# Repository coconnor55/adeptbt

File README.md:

# AdeptBT

Credit-card sized nRF52840 control board (Raytac MDBT50Q-1MV2).

## Features

- Dual TMC2209 stepper drivers
- Two 2N2222 low-side outputs with jumperable V+ (3.3 V / VIN)
- USB-C programming; LiPo (JST) with ~400–500 mA charge; VIN 5–18 V (P-FET + TVS + PPTC)
- Analog header (4× AIN at 3.3 V; external divider if needed) and digital GPIO header
- 6-pin screw terminals: steppers (`A1 A2 B1 B2 VM GND`) and power/outs (`VIN GND V+ OUT1 V+ OUT2`)

## Hardware

KiCad project: [`hardware/`](hardware/) — schematic, PCB placement, silkscreen (rev 2.0).

See [`docs/DESIGN.md`](docs/DESIGN.md), [`docs/STACKUP.md`](docs/STACKUP.md), [`docs/DECOUPLING.md`](docs/DECOUPLING.md), [`docs/JLCPCB_BOM.md`](docs/JLCPCB_BOM.md), [`hardware/README.md`](hardware/README.md). Repo decisions and open work: [`memory/`](memory/).

Open `hardware/adeptbt.kicad_pro` in KiCad 10 to finish power discretes, routing, and Gerbers.

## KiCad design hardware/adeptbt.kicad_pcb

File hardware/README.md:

# AdeptBT hardware (rev 2.0)

KiCad 10 project — JLCPCB-first. Schematic: `tools/gen_adeptbt_sch.py` if needed. **PCB placement is owned by pcbnew** (`adeptbt.kicad_pcb`). Do not run `tools/gen_adeptbt_pcb.py` — it refuses to write.

| File | Purpose |
|------|---------|
| `adeptbt.kicad_pro` | Project |
| `adeptbt.kicad_sch` | Wired schematic (global labels + GPIO lock) |
| `adeptbt.kicad_pcb` | Board (edit in KiCad; source of truth for placement) |
| `fp-lib-table` / `sym-lib-table` | AdeptBT + jlc libraries |
| `libs/AdeptBT.pretty/` | TE 3.81 mm screw, barrel 5.5×2.1, USB-C, JST, headers, M2 |
| `libs/jlc/` | Raytac MDBT50Q + TMC2209 symbols/footprints (LCSC) |
| `exports/` | SVG / PDF / ERC JSON |
| `../docs/JLCPCB_BOM.md` | LCSC SKUs + keep/reconsider |
| `../docs/NETLIST.md` | Nets + GPIO lock |

## Layout (85.6 × 53.98 mm)

- **Top:** `J_STEP1` / `J_STEP2` — TE 2383941-6; may slide laterally
- **Bottom:** `J_DC` + `J_BAT` (beside DC) + `J_PWR`; may slide laterally
- **Left:** USB-C — pads/silk/fab on-board; label on the board side
- **Right:** `J_AN` / `J_DG`; U1 antenna keepout faces this edge (angle 90°)
- **Center:** U2/U3 TMC2209, `J_SWD` west of U1, `JP_V+` (1×3), `JP_VM1`/`JP_VM2` (1×2). No JP_AIN.
- **Silk rule:** no labels past Edge.Cuts. Check: `python3 tools/check_silk.py`
- **Stackup:** 4-layer — `In1`/`In2` solid GND. After placement changes in pcbnew: KiCad Python `tools/pour_gnd.py` (see `docs/STACKUP.md`)
- **TMC neighborhood:** KiCad Python `tools/route_tmc_local.py` (short locked stubs + EP vias). Then `tools/freeroute_rest.sh` for the rest (ignore GND).

## JLCPCB (rev 0.4)

- Raytac **C5118826** + TMC **C465949** → Standard + X-ray
- Screws **C3816695** (7 A); charger **MCP73871** **C5121473**; TVS **SMBJ24A** (VIN≤18 V)
- Next: wire power discretes, sense Rs, GND pour, DRC, Gerbers

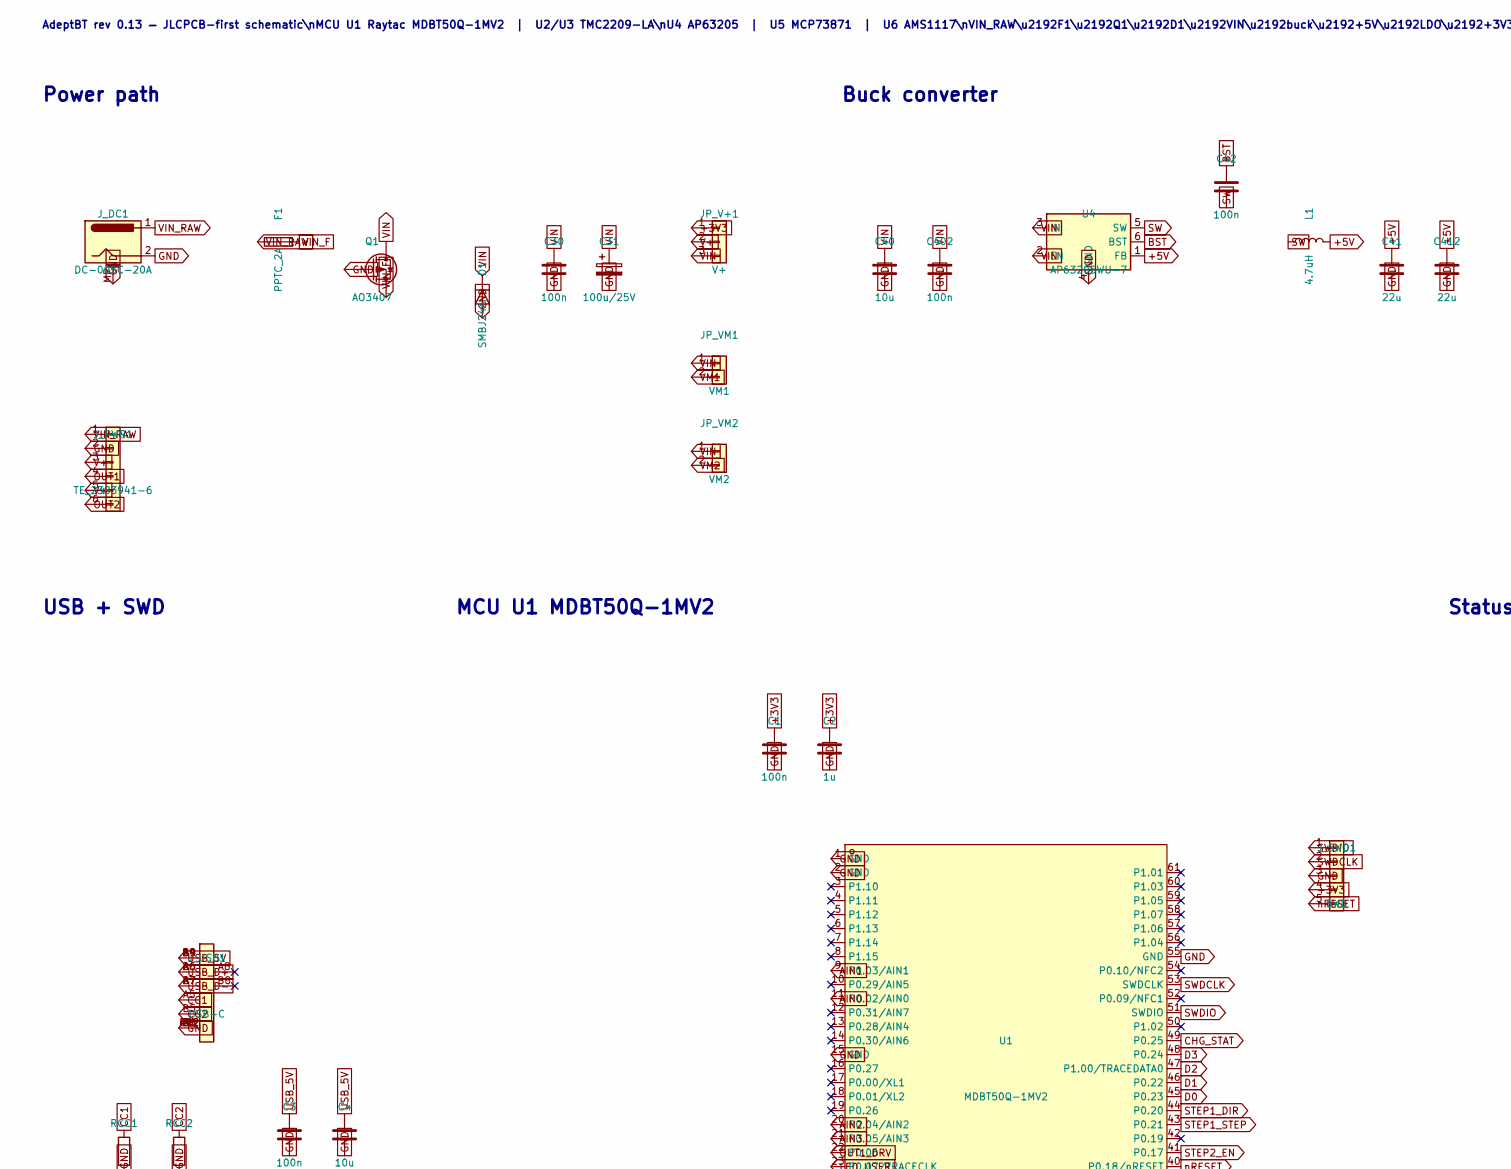
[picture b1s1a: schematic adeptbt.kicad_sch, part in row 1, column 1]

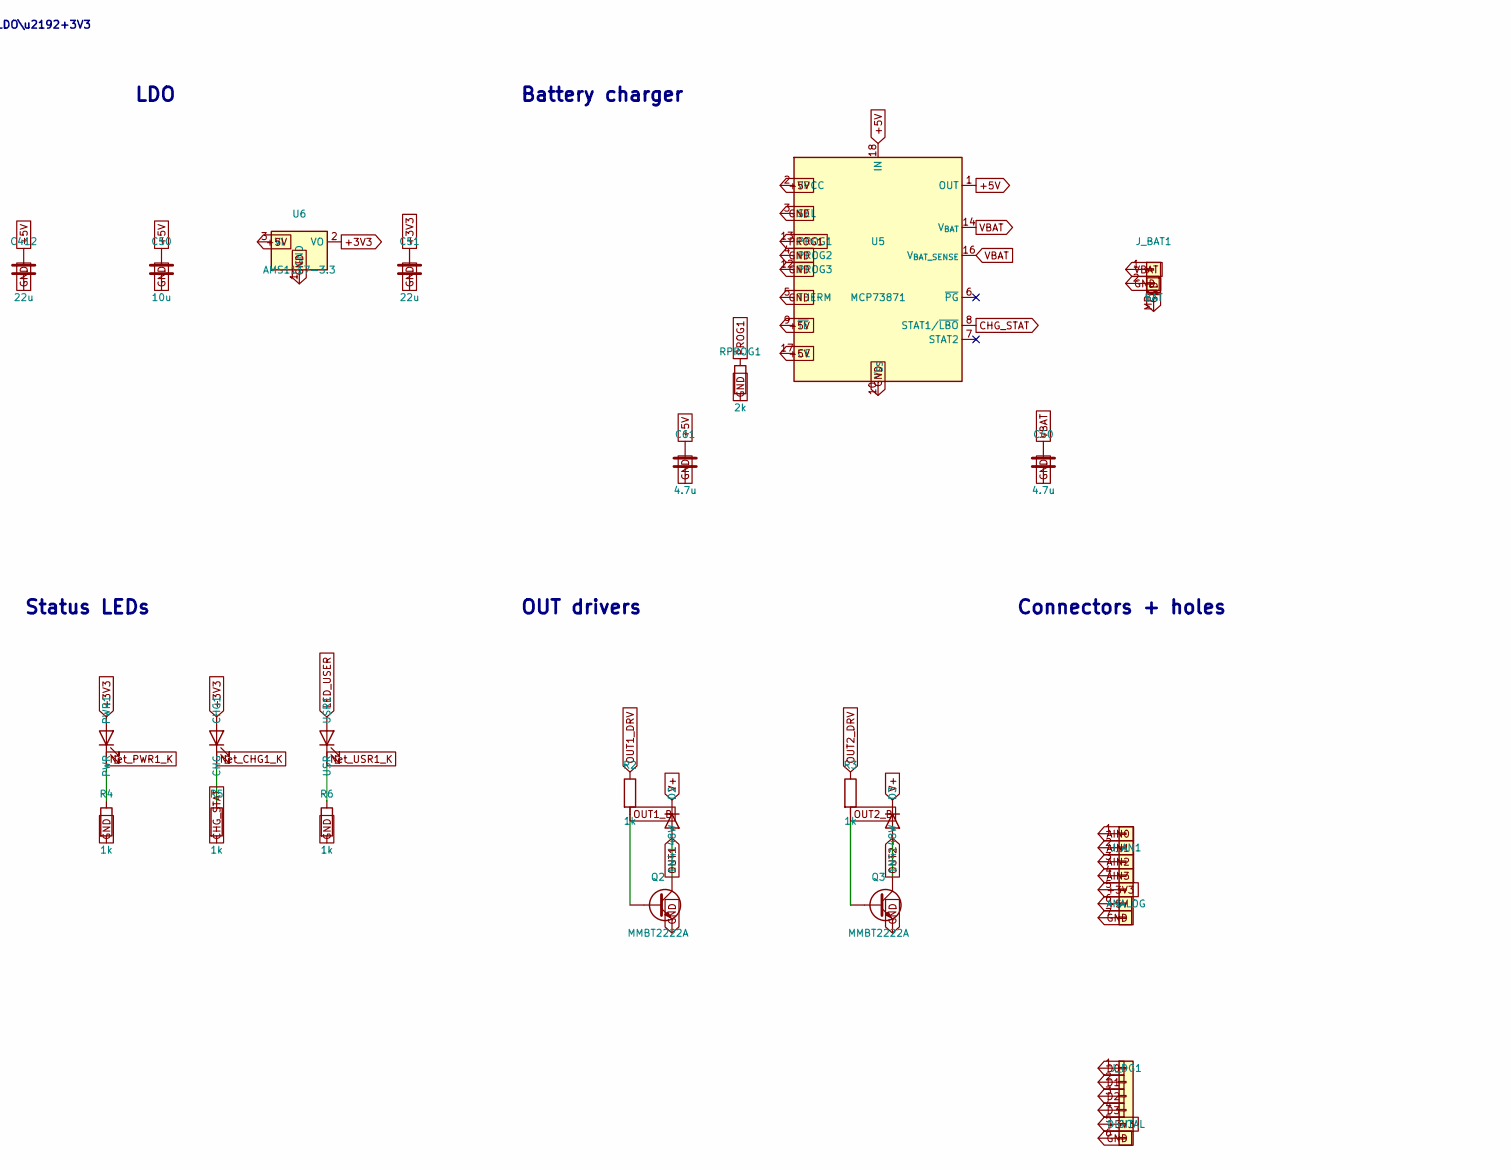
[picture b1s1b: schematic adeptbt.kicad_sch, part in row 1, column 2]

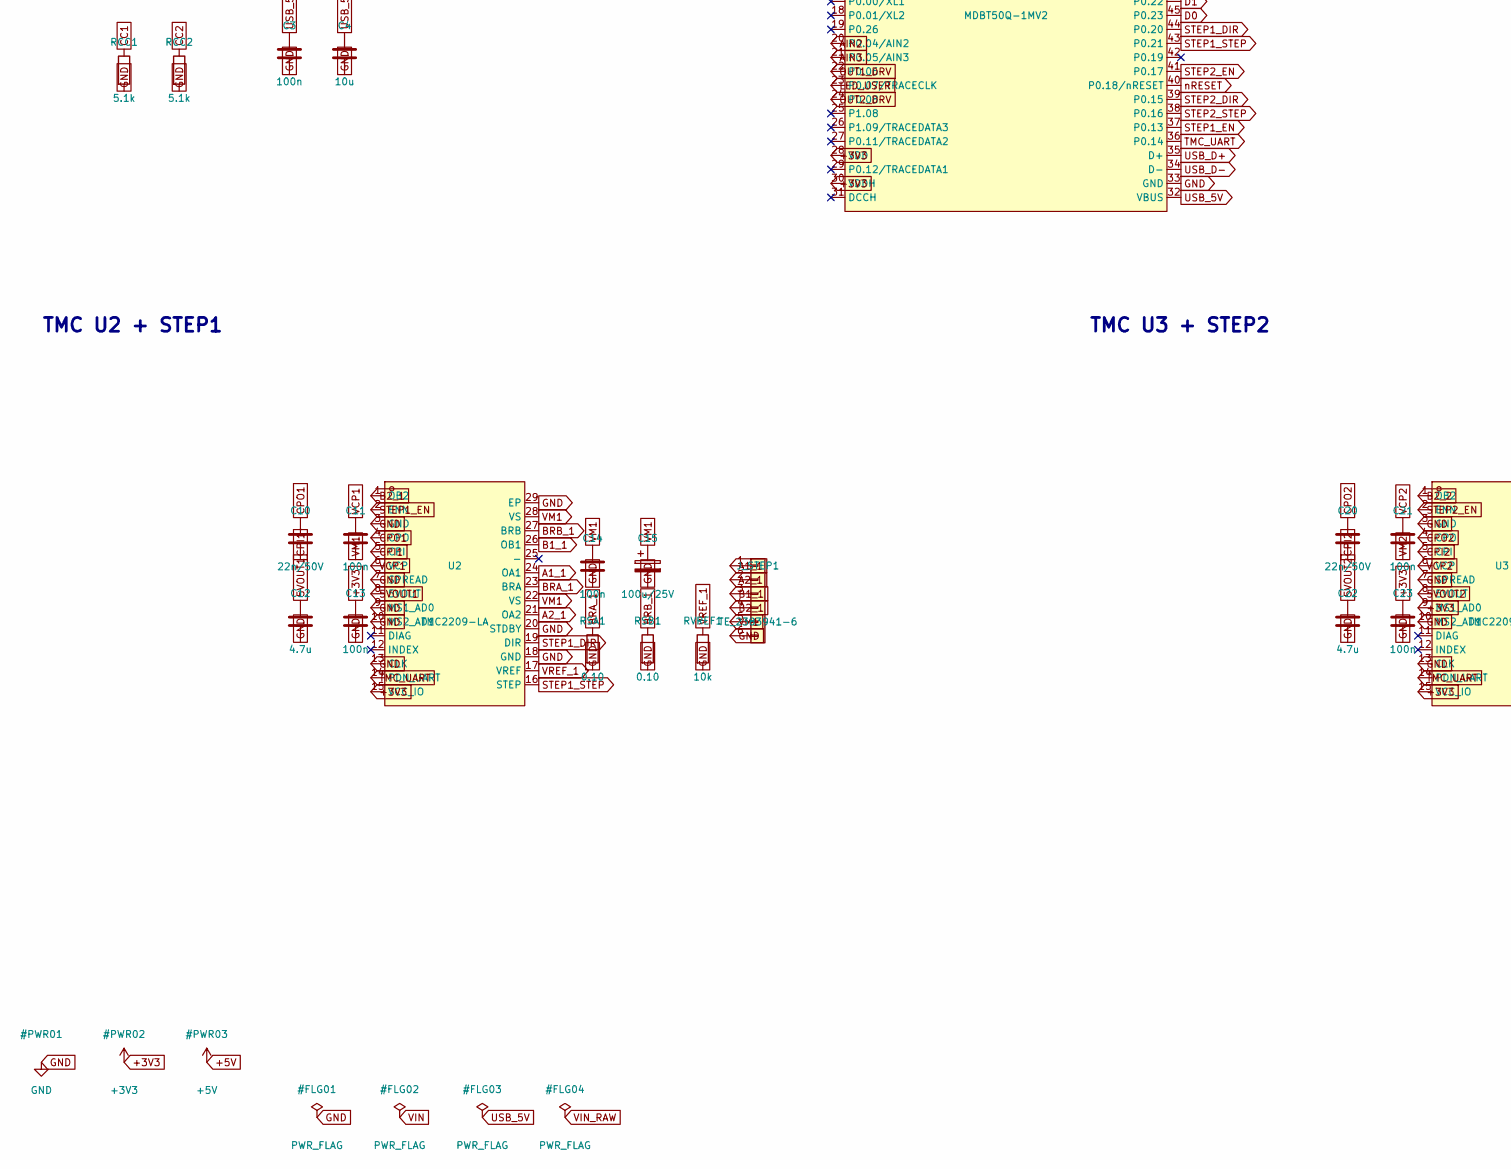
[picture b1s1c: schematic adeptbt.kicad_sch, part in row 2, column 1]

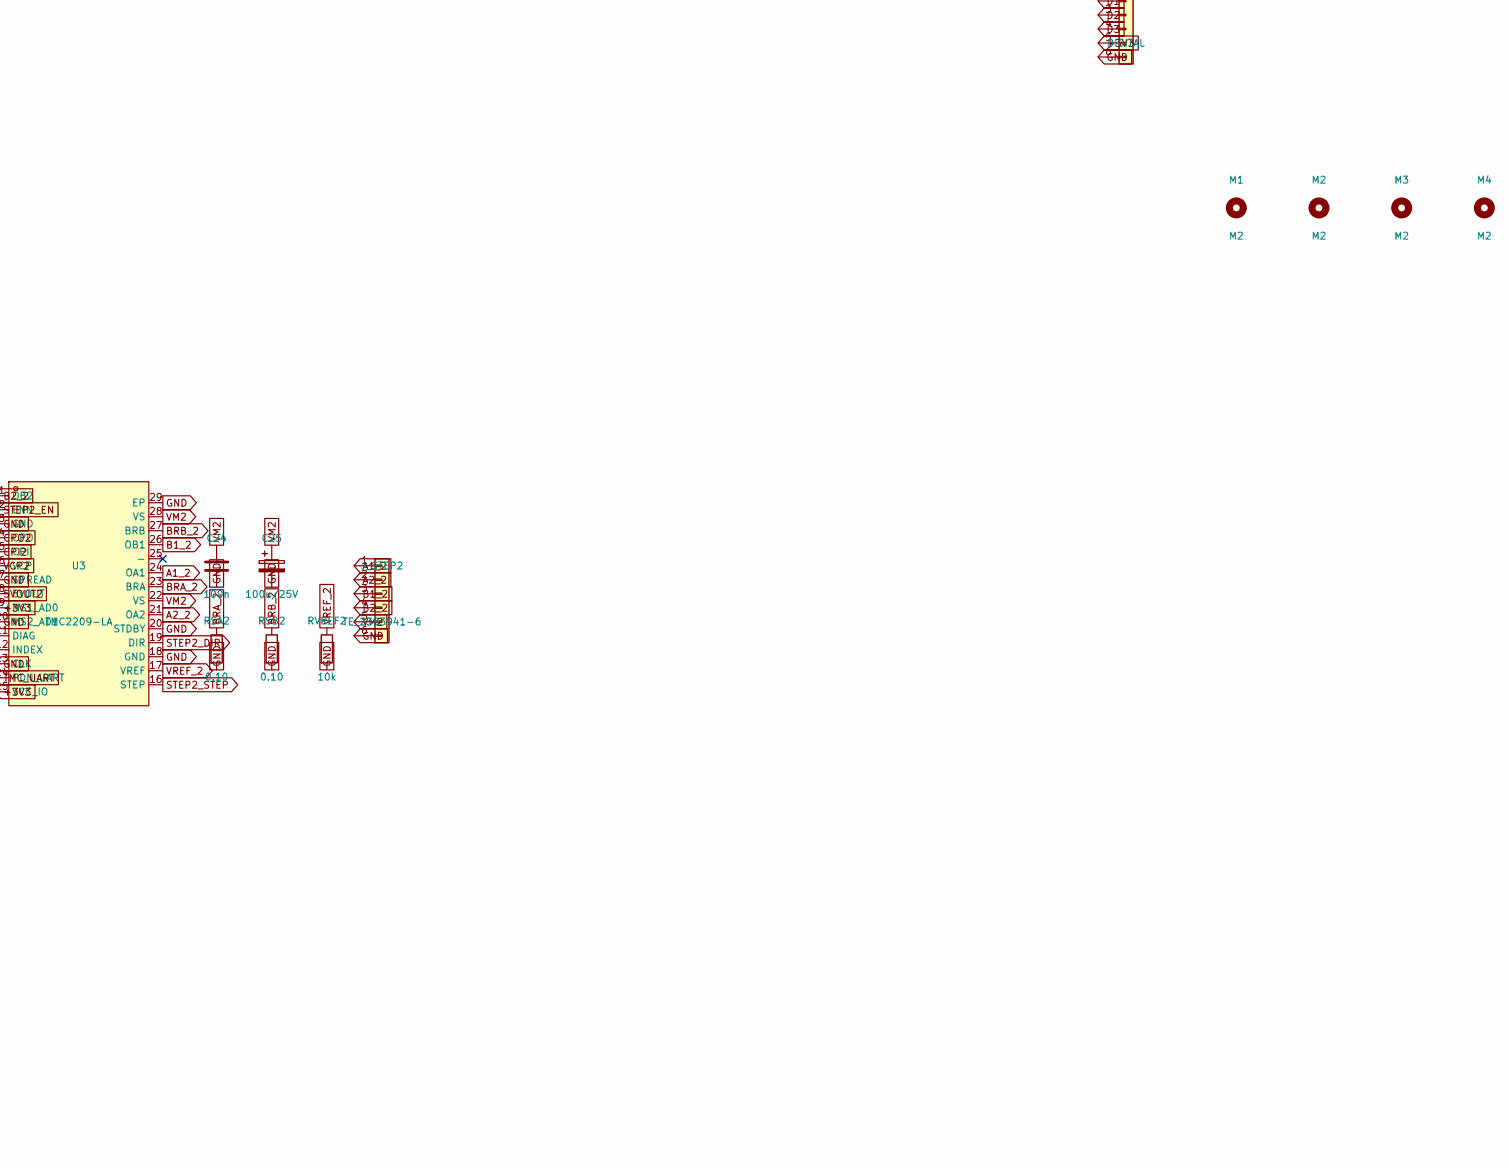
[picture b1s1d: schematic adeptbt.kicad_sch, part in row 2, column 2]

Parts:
C1, C3, C11, C13, C14, C21, C23, C24, C30, C42, C402: 100n; C_0402_1005Metric
C2: 1u; C_0603_1608Metric
C4, C40, C50: 10u; C_0805_2012Metric
C10, C20: 22n/50V; C_0603_1608Metric
C12, C22, C60, C61: 4.7u; C_0805_2012Metric
C15, C25, C31: 100u/25V; CP_Elec_6.3x5.3
C41, C51, C412: 22u; C_0805_2012Metric
CHG1: CHG; LED_0603_1608Metric
D1: SMBJ24A; D_SMB
D2, D3: 1N4148W; D_SOD-123
F1: PPTC_2A; Fuse_1812_4532Metric
JP_V+1: V+; PinHeader_1x03_P2.54mm_Vertical
JP_VM1: VM1; PinHeader_1x02_P2.54mm_Vertical
JP_VM2: VM2; PinHeader_1x02_P2.54mm_Vertical
J_AN1: ANALOG; PinHeader_1x07_P2.54mm_Vertical
J_BAT1: BAT; JST_PH_S2B-PH-SM4-TB_1x02-1MP_P2.00mm_Horizontal
J_DC1: DC-005C-20A; BarrelJack_HRO_DC-005C-20A_Horizontal
J_DG1: DIGITAL; PinHeader_1x06_P2.54mm_Vertical
J_PWR1: TE_2383941-6; TE_2383945-6_1x06_P3.81mm_SMD
J_STEP1, J_STEP2: TE_2383941-6; TE_2383945-6_1x06_P3.81mm_SMD
J_SWD1: SWD; PinHeader_1x05_P2.54mm_Vertical
J_USB1: USB-C; USB_C_Receptacle_GCT_USB4105-xx-A_16P_TopMnt_Horizontal
L1: 4.7uH; L_6.3x6.3_H3
M1, M2, M3, M4: M2; MountingHole_2.2mm_M2
PWR1: PWR; LED_0603_1608Metric
Q1: AO3407; SOT-23
Q2, Q3: MMBT2222A; SOT-23
R2, R3, R4, R5, R6: 1k; R_0603_1608Metric
RCC1, RCC2: 5.1k; R_0603_1608Metric
RPROG1: 2k; R_0603_1608Metric
RSA1, RSA2: 0.10; R_1206_3216Metric
RSB1, RSB2: 0.10; R_1206_3216Metric
RVREF1, RVREF2: 10k; R_0603_1608Metric
U1: MDBT50Q-1MV2; COMM-SMD_MDBT50Q-1MV2-1
U2, U3: TMC2209-LA; QFN-28_L5.0-W5.0-P0.50-BL-EP
U4: AP63205WU-7; TSOT-23-6
U5: MCP73871; QFN-20-1EP_4x4mm_P0.5mm_EP2.5x2.5mm
U6: AMS1117-3.3; SOT-223-3_TabPin2
USR1: USR; LED_0603_1608Metric

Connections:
5VOUT1: C12.1, U2.8 (5VOUT)
5VOUT2: C22.1, U3.8 (5VOUT)
+3V3: C1.1, C2.1, C13.1, C23.1, C51.1, CHG1.2 (A), JP_V+1.1, J_AN1.5, J_DG1.5, J_SWD1.4, PWR1.2 (A), U1.28 (VDD), U1.30 (VDDH), U2.15 (VCC_IO), U3.9 (MS1_AD0), U3.15 (VCC_IO), U6.2 (VO)
+5V: C41.1, C50.1, C61.1, C412.1, J_AN1.6, L1.2, U4.1 (FB), U5.1 (OUT), U5.2 (VPCC), U5.9 (~TE), U5.17 (CE), U5.18 (IN), U5.19 (IN), U5.20 (OUT), U6.3 (VI)
A1_1: J_STEP1.1, U2.24 (OA1)
A1_2: J_STEP2.1, U3.24 (OA1)
A2_1: J_STEP1.2, U2.21 (OA2)
A2_2: J_STEP2.2, U3.21 (OA2)
AIN0: J_AN1.1, U1.11 (P0.02/AIN0)
AIN1: J_AN1.2, U1.9 (P0.03/AIN1)
AIN2: J_AN1.3, U1.20 (P0.04/AIN2)
AIN3: J_AN1.4, U1.21 (P0.05/AIN3)
B1_1: J_STEP1.3, U2.26 (OB1)
B1_2: J_STEP2.3, U3.26 (OB1)
B2_1: J_STEP1.4, U2.1 (OB2)
B2_2: J_STEP2.4, U3.1 (OB2)
BRA_1: RSA1.1, U2.23 (BRA)
BRA_2: RSA2.1, U3.23 (BRA)
BRB_1: RSB1.1, U2.27 (BRB)
BRB_2: RSB2.1, U3.27 (BRB)
BST: C42.1, U4.6 (BST)
CC1: J_USB1.A5 (CC1), RCC1.1
CC2: J_USB1.B5 (CC2), RCC2.1
CHG_STAT: R5.2, U1.49 (P0.25), U5.8 (STAT1/~LBO)
CPI1: C10.2, U2.5 (CPI)
CPI2: C20.2, U3.5 (CPI)
CPO1: C10.1, U2.4 (CPO)
CPO2: C20.1, U3.4 (CPO)
D0: J_DG1.1, U1.45 (P0.23)
D1: J_DG1.2, U1.46 (P0.22)
D2: J_DG1.3, U1.47 (P1.00/TRACEDATA0)
D3: J_DG1.4, U1.48 (P0.24)
GND: C1.2, C2.2, C3.2, C4.2, C12.2, C13.2, C14.2, C15.2, C22.2, C23.2, C24.2, C25.2, C30.2, C31.2, C40.2, C41.2, C50.2, C51.2, C60.2, C61.2, C402.2, C412.2, D1.2 (A), J_AN1.7, J_BAT1.2, J_BAT1.MP (MountPin), J_DC1.2, J_DC1.MP (MountPin_MP), J_DG1.6, J_PWR1.2, J_STEP1.6, J_STEP2.6, J_SWD1.3, J_USB1.A1 (GND), J_USB1.A12 (GND), J_USB1.B1 (GND), J_USB1.B12 (GND), J_USB1.SH (SHIELD), Q1.1 (G), Q2.2 (E), Q3.2 (E), R4.2, R6.2, RCC1.2, RCC2.2, RPROG1.2, RSA1.2, RSA2.2, RSB1.2, RSB2.2, RVREF1.2, RVREF2.2, U1.1 (GND), U1.2 (GND), U1.15 (GND), U1.33 (GND), U1.55 (GND), U2.3 (GND), U2.7 (SPREAD), U2.9 (MS1_AD0), U2.10 (MS2_AD1), U2.13 (CLK), U2.18 (GND), U2.20 (STDBY), U2.29 (EP), U3.3 (GND), U3.7 (SPREAD), U3.10 (MS2_AD1), U3.13 (CLK), U3.18 (GND), U3.20 (STDBY), U3.29 (EP), U4.4 (GND), U5.3 (SEL), U5.4 (PROG2), U5.5 (THERM), U5.10 (V_{SS}), U5.11 (V_{SS}), U5.12 (PROG3), U5.21 (V_{SS}), U6.1 (GND)
LED_USER: U1.23 (P0.07/TRACECLK), USR1.2 (A)
Net_CHG1_K: CHG1.1 (K), R5.1
Net_PWR1_K: PWR1.1 (K), R4.1
Net_USR1_K: R6.1, USR1.1 (K)
OUT1: D2.2 (A), J_PWR1.4, Q2.3 (C)
OUT1_B: Q2.1 (B), R2.2
OUT1_DRV: R2.1, U1.22 (P0.06)
OUT2: D3.2 (A), J_PWR1.6, Q3.3 (C)
OUT2_B: Q3.1 (B), R3.2
OUT2_DRV: R3.1, U1.24 (P0.08)
PROG1: RPROG1.1, U5.13 (PROG1)
STEP1_DIR: U1.44 (P0.20), U2.19 (DIR)
STEP1_EN: U1.37 (P0.13), U2.2 (ENN)
STEP1_STEP: U1.43 (P0.21), U2.16 (STEP)
STEP2_DIR: U1.39 (P0.15), U3.19 (DIR)
STEP2_EN: U1.41 (P0.17), U3.2 (ENN)
STEP2_STEP: U1.38 (P0.16), U3.16 (STEP)
SW: C42.2, L1.1, U4.5 (SW)
SWDCLK: J_SWD1.2, U1.53 (SWDCLK)
SWDIO: J_SWD1.1, U1.51 (SWDIO)
TMC_UART: U1.36 (P0.14), U2.14 (PDN_UART), U3.14 (PDN_UART)
USB_5V: C3.1, C4.1, J_USB1.A4 (VBUS), J_USB1.A9 (VBUS), J_USB1.B4 (VBUS), J_USB1.B9 (VBUS), U1.32 (VBUS)
USB_D+: J_USB1.A6 (D+), J_USB1.B6 (D+), U1.35 (D+)
USB_D-: J_USB1.A7 (D-), J_USB1.B7 (D-), U1.34 (D-)
V+: D2.1 (K), D3.1 (K), JP_V+1.2, J_PWR1.3, J_PWR1.5
VBAT: C60.1, J_BAT1.1, U5.14 (V_{BAT}), U5.15 (V_{BAT}), U5.16 (V_{BAT_SENSE})
VCP1: C11.1, U2.6 (VCP)
VCP2: C21.1, U3.6 (VCP)
VIN: C30.1, C31.1, C40.1, C402.1, D1.1 (K), JP_V+1.3, JP_VM1.1, JP_VM2.1, Q1.3 (D), U4.2 (EN), U4.3 (IN)
VIN_F: F1.2, Q1.2 (S)
VIN_RAW: F1.1, J_DC1.1, J_PWR1.1
VM1: C11.2, C14.1, C15.1, JP_VM1.2, J_STEP1.5, U2.22 (VS), U2.28 (VS)
VM2: C21.2, C24.1, C25.1, JP_VM2.2, J_STEP2.5, U3.22 (VS), U3.28 (VS)
VREF_1: RVREF1.1, U2.17 (VREF)
VREF_2: RVREF2.1, U3.17 (VREF)
nRESET: J_SWD1.5, U1.40 (P0.18/nRESET)

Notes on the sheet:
Power path
AdeptBT rev 0.13 — JLCPCB-first schematic\nMCU U1 Raytac MDBT50Q-1MV2 | U2/U3 TMC2209-LA\nU4 AP63205 | U5 MCP73871 | U6 AMS1117\nVIN_RAW\u2192F1\u2192Q1\u2192D1\u2192VIN\u2192buck\u2192+5V\u2192LDO\u2192+3V3
Buck converter
LDO
Battery charger
MCU U1 MDBT50Q-1MV2
USB + SWD
Status LEDs
OUT drivers
TMC U2 + STEP1
TMC U3 + STEP2
Connectors + holes

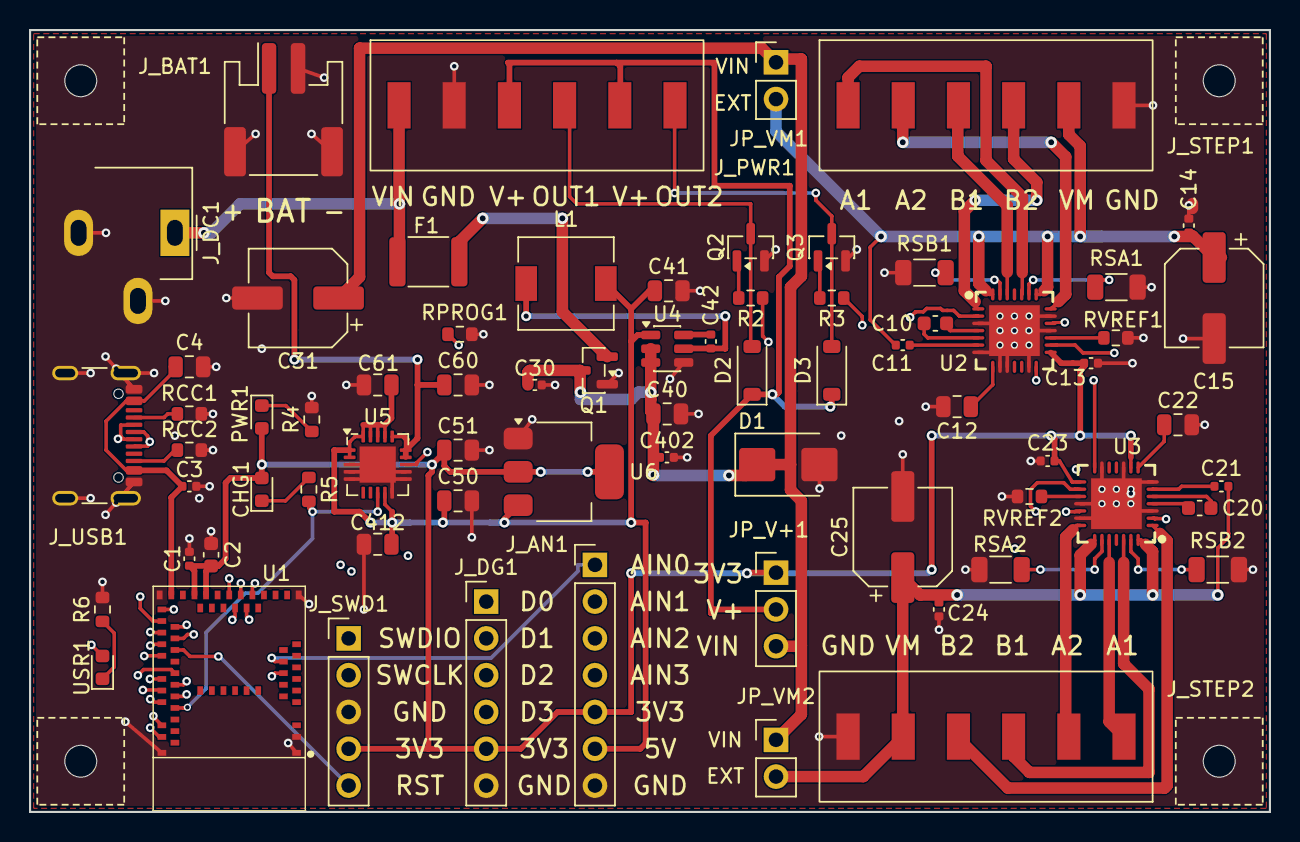
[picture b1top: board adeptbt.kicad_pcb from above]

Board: 4 copper layers, 85.6 x 54.0 mm, 74 parts (0 on the bottom side), 69 nets.

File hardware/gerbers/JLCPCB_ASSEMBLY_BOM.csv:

Comment,Designator,Footprint,LCSC Part #,Quantity,Value,MPN,Process,Notes
1N4148W,"D2,D3",D_SOD-123,C81598,2,1N4148W,1N4148W,SMT,Basic
TE 2383941-6,"J_PWR1,J_STEP1,J_STEP2",TE_2383945-6_1x06_P3.81mm_SMD,C3816695,3,TE_2383941-6,TE 2383941-6,SMT,SMD screw 7A; Extended — check stock/shortfall
MMBT2222A,"Q2,Q3",SOT-23,C8512,2,MMBT2222A,MMBT2222A,SMT,Basic
MDBT50Q-1MV2,U1,COMM-SMD_MDBT50Q-1MV2-1,C5118826,1,MDBT50Q-1MV2,MDBT50Q-1MV2,SMT,Extended; Standard PCBA + X-ray; IC; check stock
TMC2209-LA,"U2,U3",QFN-28_L5.0-W5.0-P0.50-BL-EP,C465949,2,TMC2209-LA,TMC2209-LA,SMT,Extended; X-ray; IC; check stock
AP63205WU-7,U4,TSOT-23-6,C2071056,1,AP63205WU-7,AP63205WU-7,SMT,Extended; IC
MCP73871,U5,QFN-20-1EP_4x4mm_P0.5mm_EP2.5x2.5mm,C5121473,1,MCP73871,MCP73871,SMT,Extended; IC
AMS1117-3.3,U6,SOT-223-3_TabPin2,C6186,1,AMS1117-3.3,AMS1117-3.3,SMT,Basic; IC
100n 0402,"C1,C3,C11,C13,C14,C21,C23,C24,C30,C42,C402",C_0402_1005Metric,C1525,11,100n,CL05B104KO5NNNC,SMT,Basic 0402 — do not use 01005
22n 50V 0603,"C10,C20",C_0603_1608Metric,C21122,2,22n/50V,CL10B223KB8NNNC,SMT,Basic
4.7u 0805,"C12,C22,C60,C61",C_0805_2012Metric,C1779,4,4.7u,CL21A475KAQNNNE,SMT,Basic
100u 25V 6.3x5.3,"C15,C25,C31",CP_Elec_6.3x5.3,C4747964,3,100u/25V,RST100UF25V004,SMT,Extended SMD elec D6.3xL5.4
1u 0603,C2,C_0603_1608Metric,C15849,1,1u,CL10A105KB8NNNC,SMT,Basic
10u 0805,"C4,C40,C50",C_0805_2012Metric,C15850,3,10u,CL21A106KAYNNNE,SMT,Basic
22u 0805,"C41,C51,C412",C_0805_2012Metric,C45783,3,22u,CL21A226MAQNNNE,SMT,Basic
LED 0603 red,CHG1,LED_0603_1608Metric,C2286,1,CHG,KT-0603R,SMT,Basic red; recolor at order if desired
SMBJ24A,D1,D_SMB,C5178956,1,SMBJ24A,SMBJ24A,SMT,Extended TVS
PPTC 2A 1812,F1,Fuse_1812_4532Metric,C2760293,1,PPTC_2A,SMD1812-200C-30V,SMT,Extended 2A hold 30V
JST-PH 2P SMD,J_BAT1,JST_PH_S2B-PH-SM4-TB_1x02-1MP_P2.00mm_Horizontal,C295747,1,BAT,S2B-PH-SM4-TB,SMT,Extended; DNP OK wall-wart SKU
GCT USB4105-GF-A,J_USB1,USB_C_Receptacle_GCT_USB4105-xx-A_16P_TopMnt_Horizontal,C3020560,1,USB-C,USB4105-GF-A,SMT,Extended mid-mount USB-C
4.7uH 6.3x6.3,L1,L_6.3x6.3_H3,C703091,1,4.7uH,LQH66SN4R7M03L,SMT,Extended buck inductor
LED 0603 red,PWR1,LED_0603_1608Metric,C2286,1,PWR,KT-0603R,SMT,Basic red; recolor at order if desired
AO3407,Q1,SOT-23,C22751455,1,AO3407,AO3407,SMT,Extended P-FET
1k 0603,"R2,R3,R4,R5,R6",R_0603_1608Metric,C21190,5,1k,0603WAF1001T5E,SMT,Basic
5.1k 0603,"RCC1,RCC2",R_0603_1608Metric,C23186,2,5.1k,0603WAF5101T5E,SMT,Basic
2k 0603,RPROG1,R_0603_1608Metric,C22975,1,2k,0603WAF2001T5E,SMT,Basic
0.10ohm 1206 SMD,"RSA1,RSA2,RSB1,RSB2",R_1206_3216Metric,C346768,4,0.10,CSR1206FKR100,SMT,Extended SMD 0.10Ω ±1% 0.5W sense — not THT
10k 0603,"RVREF1,RVREF2",R_0603_1608Metric,C25804,2,10k,0603WAF1002T5E,SMT,Basic
LED 0603 red,USR1,LED_0603_1608Metric,C2286,1,USR,KT-0603R,SMT,Basic red; recolor at order if desired
PinHeader 1x03,JP_V+1,PinHeader_1x03_P2.54mm_Vertical,C49257,1,V+,2.54-1*3P,THT,Extended wave; BOOMELE 1x3 male
PinHeader 1x02,"JP_VM1,JP_VM2",PinHeader_1x02_P2.54mm_Vertical,C492401,2,VM,PZ254V-11-02P,THT,Extended wave; XFCN 1x2 male
PinHeader 1x07,J_AN1,PinHeader_1x07_P2.54mm_Vertical,C6332200,1,ANALOG,HB-PH3-25417PB2GOP,THT,Extended wave; Hanbo 1x7 male
Barrel DC-005C THT,J_DC1,BarrelJack_CUI_PJ-063AH_Horizontal,C84007,1,DC-005C-20A,DC-005C-20A,THT,Extended wave; HRO 3A 5.5x2.0 mate — footprint still PJ-063AH until PCB swap
PinHeader 1x06,J_DG1,PinHeader_1x06_P2.54mm_Vertical,C37208,1,DIGITAL,2.54-1x6P,THT,Extended wave; BOOMELE 1x6 male — NOT an isolator
PinHeader 1x05,J_SWD1,PinHeader_1x05_P2.54mm_Vertical,C6332198,1,SWD,HB-PH3-25415PB2GOP,THT,Extended wave; Hanbo 1x5 male
Jumper shunt 2.54 1x2,"JP_V+1,JP_VM1,JP_VM2",,C100114,3,SHUNT,2.54 capped,Accessory,Loose 2-pin shunts x3 (V+ select + VM1 + VM2); not in CPL; hand-fit after headers
